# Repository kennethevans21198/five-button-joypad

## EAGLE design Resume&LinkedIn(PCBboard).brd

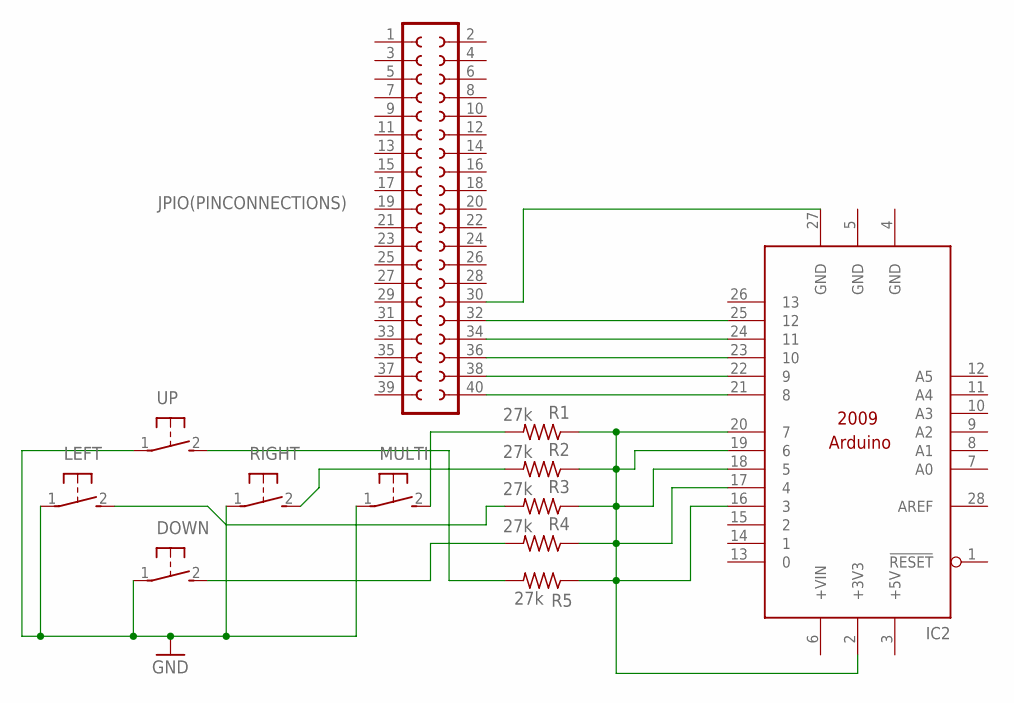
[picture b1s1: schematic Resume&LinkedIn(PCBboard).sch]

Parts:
DOWN: 31-XX; B3F-31XX
IC2: ARDUINO2009_10; ARDUINO2009
JPIO(PINCONNECTIONS): SOCKET-40V; S40V
LEFT: 31-XX; B3F-31XX
MULTI: 31-XX; B3F-31XX
R1, R2, R3, R4, R5: 27k; 0204/5
RIGHT: 31-XX; B3F-31XX
UP: 31-XX; B3F-31XX

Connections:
+5V: IC2.3 (+5V)
GND: DOWN.1, IC2.4 (GND), IC2.5 (GND), LEFT.1, MULTI.1, RIGHT.1, UP.1
unnamed: IC2.21 (8), JPIO(PINCONNECTIONS).40
unnamed: IC2.22 (9), JPIO(PINCONNECTIONS).38
unnamed: IC2.23 (10), JPIO(PINCONNECTIONS).36
unnamed: IC2.24 (11), JPIO(PINCONNECTIONS).34
unnamed: IC2.25 (12), JPIO(PINCONNECTIONS).32
unnamed: IC2.27 (GND), JPIO(PINCONNECTIONS).30
unnamed: IC2.2 (+3V3), IC2.16 (3), IC2.17 (4), IC2.18 (5), IC2.19 (6), IC2.20 (7), R1.1, R2.1, R3.1, R4.1, R5.1
unnamed: R5.2, UP.2 (S)
unnamed: DOWN.2 (S), R4.2
unnamed: LEFT.2 (S), R3.2
unnamed: R2.2, RIGHT.2 (S)
unnamed: MULTI.2 (S), R1.2

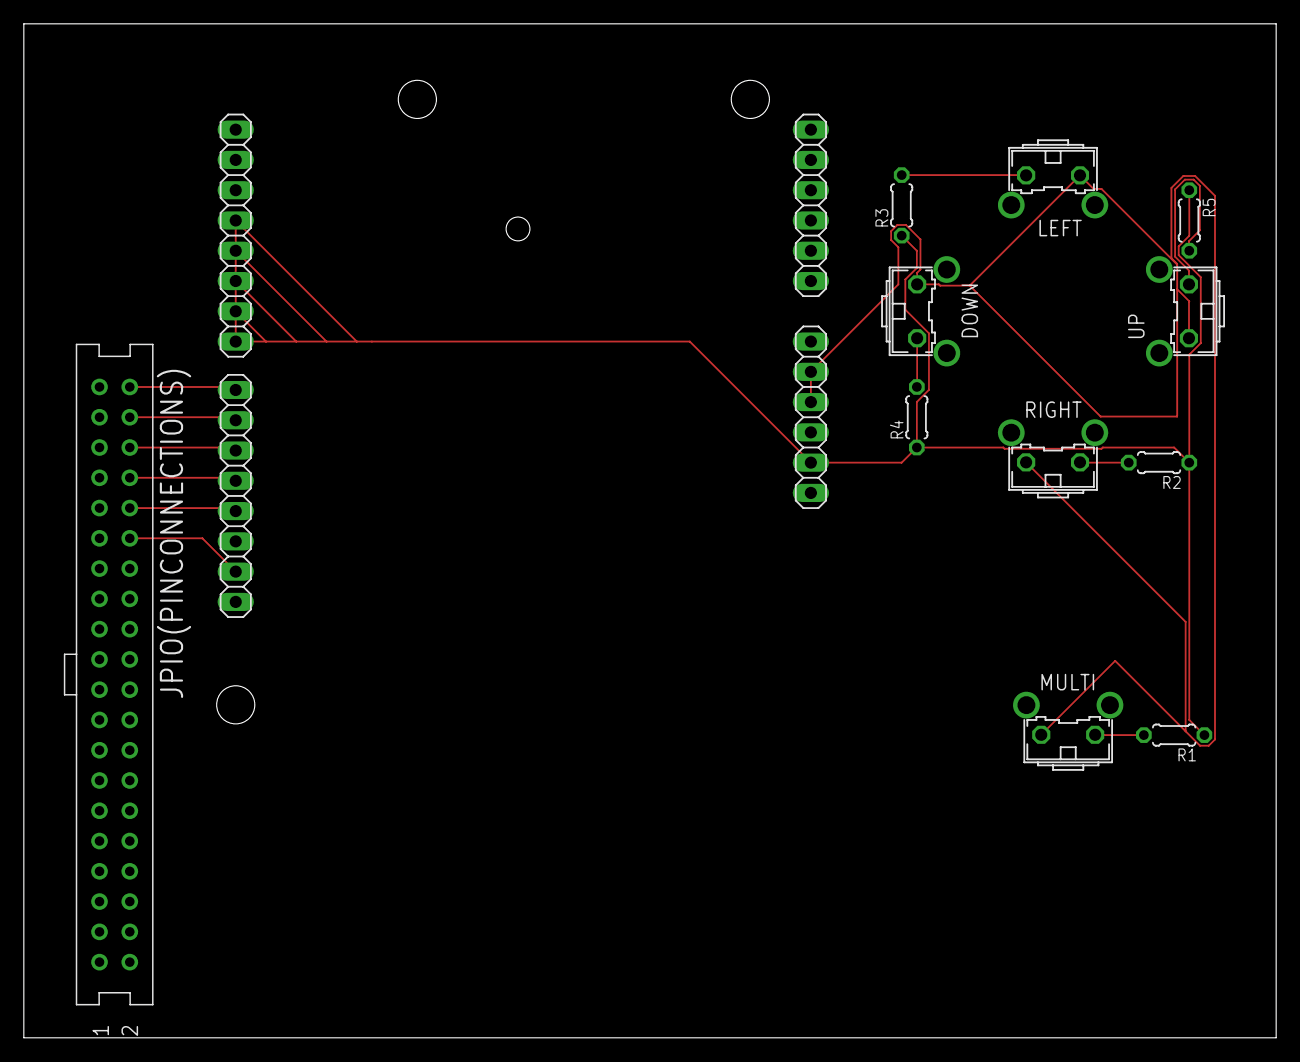
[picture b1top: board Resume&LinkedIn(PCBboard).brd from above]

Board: 2 copper layers, 105.1 x 85.1 mm, 12 parts (0 on the bottom side), 13 nets.
